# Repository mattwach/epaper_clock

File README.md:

# EPaper Clock and Weather Station

This project is an EPaper clock and weather station that automatically sets
itself (via GPS) and can be built to last about 6 months on 4 AAA batteries.
It purposefully does not need any network connections for the sake of security
and reliability.

Here is a video overview:

Features include:

   * Autoset (via GPS)
   * Current temperature.
   * Current humidity.
   * A pressure graph showing pressure over the last 25 hours.
   * Sunrise and Sunset times
   * Current moon phase
   * Select between 12h or 24h modes.
   * Select between English and metric units.

I put together two main variants of the project: "easy" and "low power".

The "easy" version is based on the Arduino Nano.  The intent with this
variation is to minimize cost and part count. The downside is that you'll need
to power the clock from a USB 5V adapter.

The "low power" version replaces the nano with a bare Atmega328P chip,
configured with a 32k crystal.  Under this configuration, the chip uses < 1
uA except when it is woken up by the crystal once per second.  This means
that the clock can be powered for a long time on batteries, even when power
draw from other devices is accounted for (all devices included draw 30-70
uA during while sleeping, and they are sleeping most of the time).

Both versions are designed to be buildable on a breadboard for experimentation.
The final board is designed to be buildable by any of several techniques:
prototype boards, CNC milling, chemical etchings, or ordering a PCB from the
provided design files are all options.

# Parts List

## "Easy" version

   * _Arduino Nano (or clone) ($3)_.  I went with a
     [clone board on Amazon](https://www.amazon.com/ELEGOO-Arduino-ATmega328P-Without-Compatible/dp/B0713XK923) but
     with April 2022 prices, I'd consider ebay as well.
   * _Waveshare 2.9 in EPaper Module ($22)_.  Purchase direct from Waveshare or
     [from amazon](https://www.amazon.com/2-9inch-Display-Module-Two-Color-Interface/dp/B07VD1V1YB).
   * _Adafruit MS8607 Pressure / Humidity / Temperature Sensor ($15)_.
     [link](https://www.adafruit.com/product/4716) I chose this one because of
     it's low power draw.
   * _Any basic GPS module with 9600 Baud TX_ ($12).  I went with
     [this one](https://smile.amazon.com/gp/product/B07P8YMVNT)
   * _Circuit Board_: This might be a
     [prototype board](https://www.amazon.com/ELEGOO-Prototype-Soldering-Compatible-Arduino/dp/B072Z7Y19F) OR
     [a piece of copper clad for CNC](https://www.amazon.com/MCIGICM-Copper-Laminate-Circuit-Single/dp/B01MCVLDDZ) OR
     you might opt to order a [prefabricated PCB](https://oshpark.com/).
   * _A couple of push switches_: [link](https://www.adafruit.com/product/1119)
     These are used to change the UTC time offset and display preferences.
   * _Materials to build a case_: I provide `.3mf`, `.scad`, and `.dxf` files
     if you would like to use a 3D printer, laser cutter, or CNC machine (I
     used a 3D printer and CNC), but you can also do a personalized case if you want.
   * _USB charger and cable_: To power the unit

## "Low Power" version

From the "easy" version above, you will need:

   * Waveshare 2.9 in EPaper Module
   * Adafruit MS8607 PHT monitor
   * Circuit board
   * Push switches
   * Case materials

You will also need

   * _Atmega328P DIP version ($2)_.
     [link](https://www.digikey.com/en/products/detail/microchip-technology/ATMEGA328P-PU/1914589)
     You can alternately opt for an SMD package version but soldering on the
     32k crystal will be harder.
   * _32768 Hz Crystal (<$1)_. [link](https://www.amazon.com/gp/product/B07Z2V95MJ)
     This oscillator is the key to low power in the design.
   * _Adafruit GPS Module ($30)_ [link](https://www.adafruit.com/product/746)
     This module is a bit higher quality than the one in the "easy" version in
     that it can track more satellites (for faster lock), provides and enable
     pin (for low power) and a port for keeping its memory active (for fast
     relock).  If all those features don't justify the added cost for you, you
     can hack a cheaper module to do the job by adding your own enable FET.  I
     explain how in upcoming steps.
   * _LED + Resistor_  The bare Atmega328P has no way to tell you if it's
     working, locked up, etc.  The blinking light thus provides a 1ms / second
     "heartbeat" that consumes almost no power but provides useful feedback.
     If you don't feel like you need it, you can omit it.
   * A couple of 10 uF and a 100 nF capacitors to smooth the power, which
     ranges from 50 uA to around 5-6 mA when refreshing the screen.
     If you feel lucky, you can try omitting these.
   * A 3x2 pin header for programming the chip via ICSP.  If you only program
     the chip off-board, you will not need this.
   * _Optional: A 1x2 pin header for UART debugging_.  You will only need this
     if the board is acting erratically.

## Arduino Mini version

I said there were two version but this is a bonus one (V2.5?).  It exists
because we live in a "parts drought" where chips like the Atmega328P go out of
stock for long periods.

You can run this version with the "easy" firmware or, if you have
the soldering confidence, you can solder a 32k crystal on the board and go with the
32k version of the firmware (more details on the next section).

Here is the schematic.  This one is wired with a "cheap GPS" solution but you
can also go with the Adafruit GPS if you replace the GPS part of the schematic
with the Adafruit setup (as illustrated in the low power schematic).

## Cheap GPS

That Adafruit GPS unit is expensive compared to the competition.  If you don't
think the added features (described above) are "worth it" you can drop in any
GPS module that transmits NMEA strings at 9600 baud (which is most of them).
**But now there is a new problem to solve:** most of these units lack an
enable/disable pin and GPS units typically consume 30-60 mA of power.  You can
hack a disable switch in using a N-MOSFET (or similar).  Here is the basic
idea:

[try it out](http://www.falstad.com/circuit/circuitjs.html?ctz=CQAgjCAMB0l3BWcMBMcUHYMGZIA4UA2ATmIxAUgoqoQFMBaMMAKADMLiUQUAWKwvx5Ds3MNCQwELAEoUMhEIIphuyqlSGSoUCSwBOSoczVCUfHZRYAPJQnJpeIDJAeuQTiwHEACgGUWACMlfHAUPGcwRRQwJ0gWAHd5RWVBATjEo3Ss8FUoFgBzHJQEFJFIOPzDBC5hTWJooSoweFkPZT5NUTqdTSpsaGxe3WkAZ3bPIV4GnuaQNgBDABtRugMPGc6NxVENZHg4Qu2QXePsbEUNFiA)

This power circuit has trade-offs.  See Appendix B for details if you are
interested in learning more about them.

## Low Power Hardware Mods

If running the "easy" version, you don't need to read this section.  For the
low power version, these mods will improve battery life significantly.

For illustration we will assume power is coming from a set of AAA batteries
which can supply 1000 mAh.  Let's assume you are using the 32k Adafruit version
and are doing no mods.  Here is an example power breakdown:

   * "Sleeping/Off" CPU, GPS, MS8607, and EPaper: Measured at 30-70 uA (we'll
     say 50uA)
   * Screen Update: 5 mA for 2 seconds once per minute: 5 * 2 / 60 = 166 uA
   * GPS Update: 50 mA for 10 seconds once per day: 50 * 10 / 86400 = 6 uA
   * MS8607 LED: 100 uA
   * Adafruit GPS pullup resistor: 500 uA

Thus we have 822 uA of average current draw which amounts to ~50 days of power.

Remove the MS8607 LED and the GPS pullup and we reduce power usage to 222 uA
which is ~187 days of power, significantly more!

### Remove the LED from the MS8607

### Remove the "pullup" enable resistor from the Adafruit GPS module (if using)

This was added by Adafruit to make the EN pin ignorable by inexperienced users.
But it has a big downside: when you pull it to ground (to disable the GPS) -
about 500uA is lost to heat in that pullup resistor!  Since the enable pin is
actively driven in the 32k oscillator design, you can remove the resistor.

### Pro mini mods

Google search "[Arduino mini low power](http://www.google.com?q=arduino%20mini%20low%20power)".
The TLDR is that you'll want to remove the voltage regulator and LED to reduce
power usage.  We are using the MS8607's voltage regulator (3.3V, 35-55 uA power
lost at idle) to power the pro mini.

In the photo above, I also removed the crystal oscillator (lower right) to prep
the chip for a 32K crystal.  This is *only* for the 32k crystal version and
*only after* the fuses have been changed on the pro mini as explained later.

## Other notes

The "easy" design actually contains the same firmware features from the 32k
design you can take advantage of if you want:

   1. D5 is still driven as a status light so you can connect an LED/Resistor
      here if you want to.
   2. D6 is still driven as a GPS enable/disable so you can use it to turn the
      GPS on/off if you want to.

# Firmware Upload

This firmware is open source and is located at [link here].

I have included prebuilt firmware `.hex` files in the `firmware/` directory so
you likely do not need to build the code.

Still want to build it and possibly add your own modifications?  Here are some
tips:

## OPTIONAL: Building the .hex firmware files yourself

Note that this code does not use Arduino libraries because the resulting code
would be too big to fit on the Atmega328P (and it's my personal preference).
Instead it's written in C using the same AVR base libraries that Arduino also
uses as a base.  If you want to compile the code, you will need to install the
(free) `avr-gcc` tools, then go to the `firmware/` directory and type

    make

If the code builds, you'll want to open the `Makefile` and look at
these options:

    # This is the Low-power stand alone chip configuration.
    CLOCK_MODE ?= USE_32K_CRYSTAL
    UART_MODE ?= HARDWARE_UART
    F_CPU ?= 8000000
    
    # This is the easy-to-build firmware that is based on an Ardino Nano
    #CLOCK_MODE ?= USE_CPU_CRYSTAL
    #UART_MODE ?= SOFTWARE_UART
    #F_CPU ?= 16000000

If you are building the 32k crystal firmware, you are done.  If building the
nano version, you'll need to comment out the 32k lines and uncomment the nano
lines, then `make` the firmware again.

There is also a special debug mode that dumps log messages over the hardware
UART at 9,600 baud.  I think you can ignore it for now but keep it in mind as
something that might be useful for troubleshooting later:

    # Uncomment to activate debug via the UART TX (9600 baud)
    #DEBUG_CFLAG := -DDEBUG

Finally, you can decide how often the GPS should be activated by changing a
couple of variables.  By default, currently runs once per day but will run less
often if GPS takes a long time to lock in order to reduce battery drain.  Read
all about it in `src/gps.c`

## ICSP hardware

This section is for those uploading code to a stand-alone Atmega328P chip (or
burning Arduino Pro mini fuses).

You'll need what is called an ISP (or ICSP) programmer.  You can buy these for
around $10 [on amazon](https://www.amazon.com/gp/product/B0885RKVMC) or make
one yourself with a spare
[Aruino Uno/Nano](https://create.arduino.cc/projecthub/arjun/programming-attiny85-with-arduino-uno-afb829)
The options continue but I'll leave that to a Google search for
"[Arduino ISP Programmer](http://www.google.com?q=Arduino%20ISP%20Programmer)".
I will note that a lot of these guides assume your real goal is to install a
bootloader but for our case, no bootloader is needed as you'll be uploading
the `.hex` file directly.

### Brownout detection

On my particular Atmega328P, the brownout detection as set to 3.5V (old version
of the chip?  A clone?) so I disabled
brownout detection with this command:

    /usr/bin/avrdude -patmega328p -cusbasp -Uefuse:w:0xFF:m

Your options may be different depending on your ISP programmer (the -c option).
You probably won't need it but just in case...

## Using avrdude

The popular Arduino IDE uses a free utility named `avrdude` to upload the hex files it creates to your
Uno/Nano/etc.  You can also download and use `avrdude` directly from the commandline
instead.  To get the correct options for the tool you can:

   1. Run an upload (blinking light demo or something) with the Arduino IDE
      with output logging turned on.  Then copy the command it used.  OR
   2. Read the official [avrdude docs](https://www.nongnu.org/avrdude/) OR
   3. Read one of the many many [avrdude tutorials](http://www.google.com?q=avrdude%20tutorial) on the internet.

For your reference, here is the `avrdude` command I used for the nano version (via `make upload`):

    /usr/bin/avrdude \
			-v \
			-patmega328p \
			-carduino \
			-P/dev/ttyUSB0 \
			-b57600 \
			-D \
			-Uflash:w:epaper_firmware_using_arduino_nano.hex:i 

and this is what I used for the ISP version:

    /usr/bin/avrdude \
			-v \
			-patmega328p \
			-cusbasp \
			-Uflash:w:epaper_firmware_using_arduino_nano.hex:i 

but there is a fair chance your setup is a bit different than mine.

## 32K Crystal

If you are building the "easy" version, skip this section.

If you are using the 32k crystal firmware, the crystal will need to be
installed for the firmware to operate.

**First (!)** You'll also want your ATMega328P set to use the internal 8 Mhz
crystal.  It's important to do this step first because the 32k crystal is using
the pins of the old crystal.  If you don't change these fuses, the chip will
become non responsive until you reconnect a 8 or 16 Mhz oscillator which
would be an annoying pain.  As far as I know the Arduino pro mini also needs
ISP to change the fuses (but I could be wrong).  I looked up "Arduino ISP" to
get the correct pin mappings for interfacing an ISP connector with a breadboard
as shown:

With my ISP programmer, I check with this command:

    $ avrdude -patmega328p -cusbasp
    ...
    avrdude: safemode: Fuses OK (E:FF, H:DE, L:E2)

The `L:E2` _is the setting you want for internal 8mhz_.  If your value is
different, you can update it with a command similar to this one:

    /usr/bin/avrdude -patmega328p -cusbasp -Ulfuse:w:0xE2:m

Then recheck.

Onto the hardware mod.  Here is a 32k crystal installed on a Atmega328P 

And on a Arduino Pro Mini (which also has the low power mods as-explained
earlier)

Attaching directly to the pins is recommended to reduce stray capacitance.  Too
much capacitance and the crystal will take longer to start oscillating (or fail
to start).

## Optional: First Steps

   * You can verify that things are OK so far on a breadboard by connecting
     just a LED/Resistor to D5 and uploading the firmware.  If all is well, the
     light will briefly flash once per second.
   * Next, you can add the EPaper display.  None of the data will be correct on
     the display but is should show something.
   * Next, add the PHT module
   * and finally the GPS module.

At this point, we are "done and can transfer everything over to a more permanent
fixture"

# Circuit Board assembly

Here you have the option of using a perf board, cutting the board with a CNC or
sending the design to a fab for manufacture.

The design files can be found in the `schematics/` directory and loaded into
Kicad.  There are three hardware flavors to choose from (all shown from behind
since that is how you would wire them by hand):

"Easy" Arduino Nano + Cheap GPS (always on)

Raw ATMega328P + Adafruit GPS (low power)

Pro Mini + Cheap GPS with MOSFET power cutoff

As can bee seen above, I cut the ATMega328P version with my CNC machine.  If
you have not used CNC to cut a PCB and are interested, try a google search for
"[3018 PCB](http://www.google.com?q=3018%20PCB)" and you'll
find many videos and articles on the topic.  I may do my own tutorial in a
separate article in the future but, since CNC is optional here it's not a good
place to go into details.  Isolation clearances are 0.4mm but you can go
narrower (probably not wider).  I used Flatcam to convert Kicad's Gerber output
to G-Code.  I included my Flatcam project in the schematic directory.  I also
included the G-Code files I sent to my 3018 CNC machine.  If you have a 3018
CNC, you can probably directly use the G-Code files, but do a "dry" run without
a bit first to make sure things look sane.

Anyway, when the circuit is finished and put together, it should function like
it did on the breadboard.  If you hold the select button on startup,
the GPS will be powered down (if possible) and you can try measuring the
current draw with your multimeter.  If you see 50-110 uA, we are seeing the
same result.  If not, you can unplug devices one at a time to try and narrow
down the parasitic power draw (assuming you didn't solder everything
permanently to the board).

# Case Design

You can design any type of case you want and I encourage you to be creative
here!  But I'll also share how I made my case and provide all of the files in
case you are interested in a more streamlined progression.

All of my design files are in the `case_design/` folder of the project.

My design uses a 3D printed support structure and two CNC parts: a top cover
and front panel.  The CNC parts are made of wood because I thought it would
look nicer than plastic.  I designed the whole thing upfront in OpenSCAD

I printed the main structure with 0.2mm layer height.  On my printer, the print
took a little over 5 hours.

I used OpenSCAD's "projection" feature to created 2D DXF files for the top
cover and front plate.  At this point, I would normally use a free program
called "Carbide Create" to make G-Code for the CNC machine.  But my face plate
has a 45 degree chamfer to the screen and Carbide Create is too basic of a
program to handle this well (at least my Google searches through forums on
    their website led me to that conclusion).  So I tried a different program
called "CamBam" and it worked very well.  CamBam is not free but you can use it
40 times for free.  I'm leaning toward purchasing the program but want to
experiment with it on a few more project first.

Some build photos:

# Appendix A: Optional Clock Drift Correction

Your 32k/CPU crystal will not be perfect.  When the GPS turns on, it will
correct the drift.  But if the drift is bad or your GPS signal is bad, you can
also apply a correction in the firmware.  This currently requires you to build
the code.

At the top of `main.c` there are some commented out defines:

    // Clock drift correction
    // If your clock runs too fast or too slow, then you can enable these
    //#define CORRECT_CLOCK_DRIFT
    // number of seconds that a second should be added or removed
    //#define CLOCK_DRIFT_SECONDS_PER_CORRECT 1800
    // define this if the clock is too slow, otherwise leave it commented out
    //#define CLOCK_DRIFT_TOO_SLOW

You can uncomment all of the `#define` statements above to enable the correction.
You only uncomment `CLOCK_DRIFT_TOO_SLOW` of your clock is falling behind.
If your clock is too fast, leave it commented.

The only thing left to do is set `CLOCK_DRIFT_SECONDS_PER_CORRECT`...

### The math way

Wait a handful of hours, then see how much the clock has drifted.  For example,
you might wait 23 hours.  If at that point you see the clock has lost 10
seconds, then your correction would be: (3600 * 23) / 10 = 8280 seconds
per correction.

    #define CORRECT_CLOCK_DRIFT
    #define CLOCK_DRIFT_SECONDS_PER_CORRECT 8280
    #define CLOCK_DRIFT_TOO_SLOW

If you already set `CLOCK_DRIFT_SECONDS_PER_CORRECT` and find you want to fine
tune it _even more_, then you need to add (if too slow) or subtract (if too
fast) `int(SECONDS_ON / CLOCK_DRIFT_SECONDS_PER_CORRECT)` to the error term
in the denominator to account for the already-corrected error seconds.
Building on the example above, if _we were still_ 2 seconds slow after 20
hours, the calculation would be.  (3600 * 20) / (int(3600 * 20 / 8280) + 2) =
7200.

### The non math way

Just try a number like 5,000 and refine it as you note that the clock is still
to fast or too slow.  Still too slow?  Try 2,500.  Too fast?  Try 10,000.  Keep
notes and iteratively refine it to some acceptable value just like the number
guessing games you may have played at some point.

# Appendix B: Cheap GPS power control (The tale of the BS170 N-MOSFET)

Revisiting the power control circuit described in the "Cheap GPS" section.

[try it out](http://www.falstad.com/circuit/circuitjs.html?ctz=CQAgjCAMB0l3BWcMBMcUHYMGZIA4UA2ATmIxAUgoqoQFMBaMMAKADMLiUQUAWKwvx5Ds3MNCQwELAEoUMhEIIphuyqlSGSoUCSwBOSoczVCUfHZRYAPJQnJpeIDJAeuQTiwHEACgGUWACMlfHAUPGcwRRQwJ0gWAHd5RWVBATjEo3Ss8FUoFgBzHJQEFJFIOPzDBC5hTWJooSoweFkPZT5NUTqdTSpsaGxe3WkAZ3bPIV4GnuaQNgBDABtRugMPGc6NxVENZHg4Qu2QXePsbEUNFiA)

The power cutoff circuit above is called a "low side switch".  It's benefit is
that it's relatively easy to understand and the part count is low.  That said,
there are some design concerns:

   * The ground of the GPS is not tied to GND but on the MOSFET drain.  This 
     means that the UART signal from the GPS to the microcontroler will have
     the MOSFET voltage drop added to it (Vds), increasing noise sensitivity
     and possibly causing outright errors. 
   * You would not want to use this design if your microcontroller inputs
     are specified as 3.3V maximum (the ATMega328P I chose doesn't have this
     limitation).
   * 3.3V (EN pin above) is not a very strong turn-on voltage for a typical MOSFET.

But hey, the UART is a digital signal and the ground difference isn't *that*
much so maybe it will work anyway?  I tried it and it worked fine... at first
but I came to discover over time that it was not reliable.  To understand
*why*, we refer to the characteristic curves of the BS170 I originally chose as
my N-MOSFET:

At 3.3V on the X axis we will be sitting between the 3.0 and 4.0V lines on the
graph.  So maybe we'll get 100mA?  Maybe enough?

My multimeter was telling me the GPS consumes 40-60ma while on but I think this
is an average value.  Depending on what the GPS was trying to do, it just
needed more current than the transistor was willing to allow, thus the GPS
ground (MOSFET drain) voltage would rise.  This created both UART errors and
reduced overall voltage to the GPS unit which would sometimes still sort of
work and other times go into a reset loop.

One solution would be to go with a "high side" with an additional P-MOSFET on
top to make it happen.  This eliminates the separate ground issue and provides
a full 5V (battery) gate voltage swing, which will turn the associated P-MOSFET
fully on:

[try it out](http://www.falstad.com/circuit/circuitjs.html?ctz=CQAgjCAMB0l3BWcMBMcUHYMGZIA4UA2ATmIxAUgoqoQFMBaMMAKADMLiUQUAWKwvx5Ds3MNCQxIKdiEFUwGQnKFgUeELwjjJsGQCcVCpRULHlC+JBYB3OX3DrTCp9bsIzjjR-NQWAJWcvTWJlNQ0qKiFJKCgJFkMMNHATJKp1CJoWAA8QHHIiDQw8AowIXmEQAHEABQBlFgAjOTwNMC480J5ivwBzPOSMgapRSL87Qg9gtOC3YenkxQtbIxTleR4Ha36NlCmN3ArIhM5uPiiu89iweADNQWEo0UfYqJHobFe4hBYAZ3uKldeJchAoQGwAIYAG1+dBYQA)

But in my optimism, I had already ordered PCBs with the lowside wiring so my
secondary solution was to abandon the BS170 and go with a FQP30N06L instead.
This higher-current MOSFET (max 30A!) seems like serious overkill, and it is
but its curves look like this:

Around 10A of current allowance at 3.3V which is a 100x improvement over the
BS170 and should now be plenty.  And indeed the instabilities have not
returned.

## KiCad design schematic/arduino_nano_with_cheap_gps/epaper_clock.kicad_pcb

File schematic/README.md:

Different Hardware Configurations:

   * `arduino_nano_with_cheap_gps`:  The "easy" design which uses a minimum part count
     and is intended to be powered with a USB power adapter.
   * `raw_atmega328p_with_adafruit_gps`: Uses raw Atmega328P and an Adafruit
       GPS unit.  A good match for the 32k oscillator firmware for long battery life.
   * `arduino_pro_mini_with_cheap_gps`: Uses an arduino pro mini with an inexpensive GPS
      unit and MOSFET shutoff.  The pro mini can be hacked with with a 32k oscillator
      (see the main README.md for more info)  

You can mix and match above, for example raw atmega328p + cheap gps, but will need to make
layout corrections (or make a simple adapter board) if you are using the PCB layout.

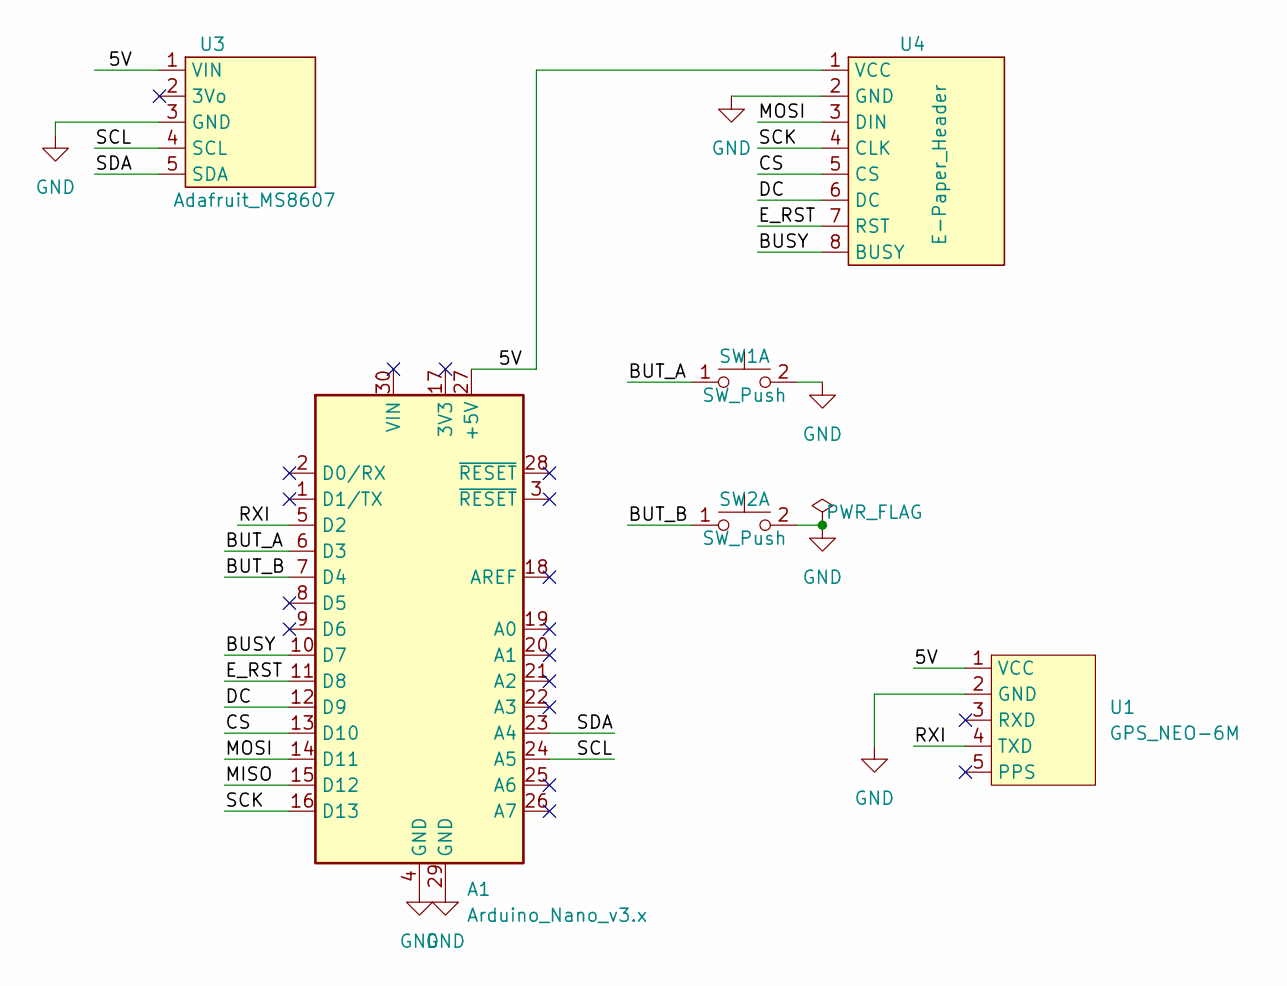
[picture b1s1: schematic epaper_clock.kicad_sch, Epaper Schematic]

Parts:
A1: Arduino_Nano_v3.x; Arduino_Nano
SW1, SW2: SW_Push; SW_TH_Tactile_Omron_B3F-10xx
U1: GPS_NEO-6M
U3: Adafruit_MS8607
U4: E-Paper_Header; PinHeader_1x08_P2.54mm_Vertical

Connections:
/5V: A1.27 (+5V), U1.1 (VCC), U3.1 (VIN), U4.1 (VCC)
/BUSY: A1.10 (D7), U4.8 (BUSY)
/BUT_A: A1.6 (D3), SW1.1 (C)
/BUT_B: A1.7 (D4), SW2.1 (C)
/CS: A1.13 (D10), U4.5 (CS)
/DC: A1.12 (D9), U4.6 (DC)
/E_RST: A1.11 (D8), U4.7 (RST)
/MISO: A1.15 (D12)
/MOSI: A1.14 (D11), U4.3 (DIN)
/RXI: A1.5 (D2), U1.4 (TXD)
/SCK: A1.16 (D13), U4.4 (CLK)
/SCL: A1.24 (A5), U3.4 (SCL)
/SDA: A1.23 (A4), U3.5 (SDA)
GND: A1.4 (GND), A1.29 (GND), SW1.2 (D), SW2.2 (D), U1.2 (GND), U3.3 (GND), U4.2 (GND)

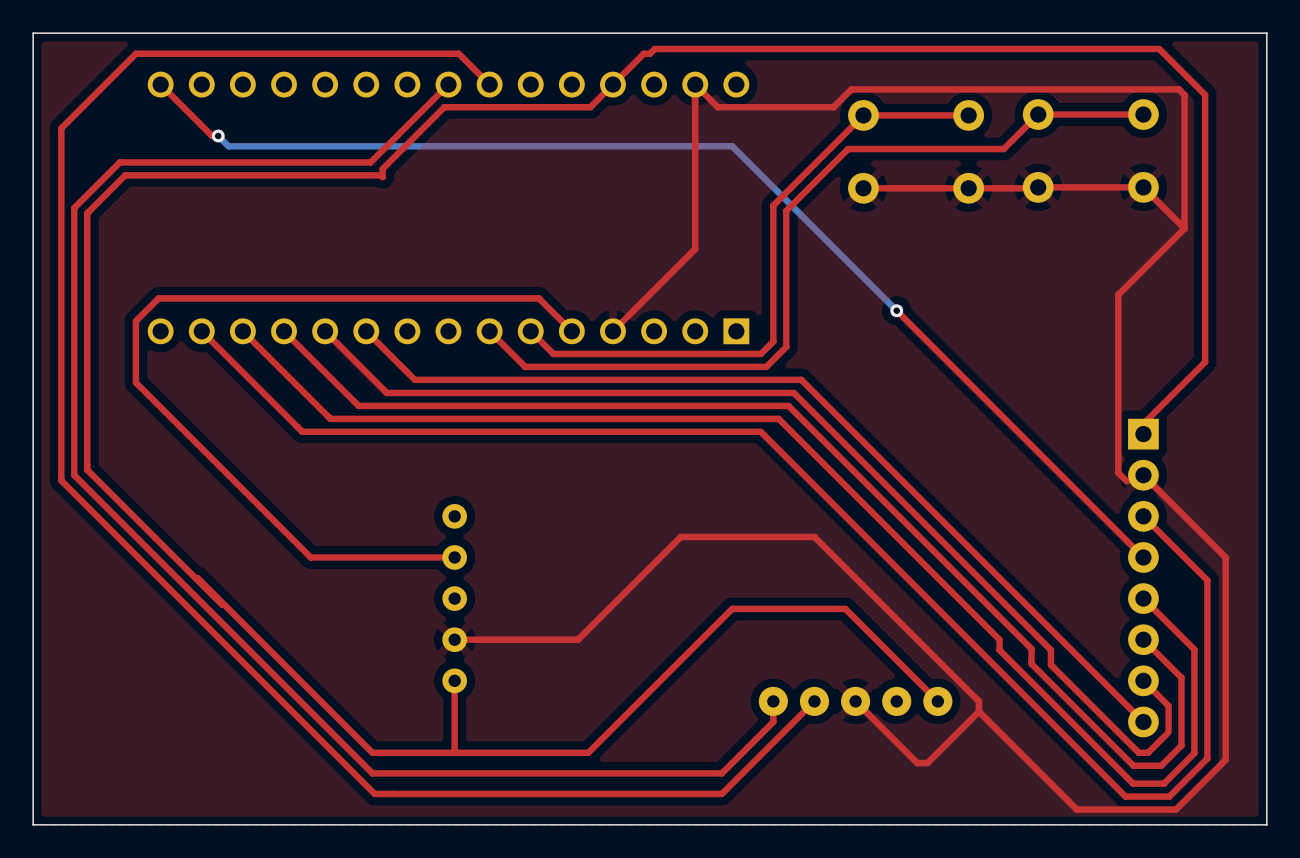
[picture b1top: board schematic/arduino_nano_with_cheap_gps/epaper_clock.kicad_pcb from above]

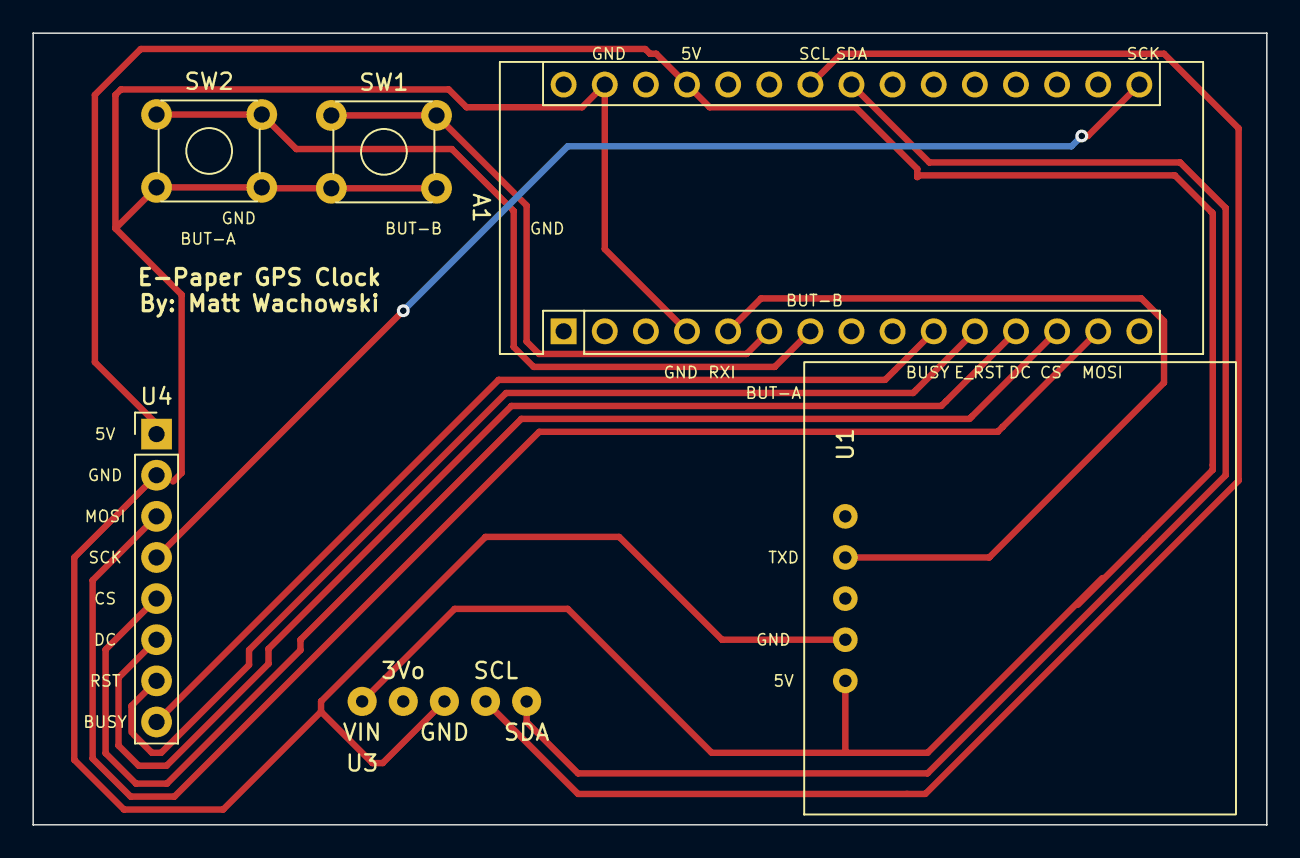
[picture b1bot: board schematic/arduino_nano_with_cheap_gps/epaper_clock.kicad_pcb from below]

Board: 2 copper layers, 76.2 x 48.9 mm, 6 parts (6 on the bottom side), 13 nets.

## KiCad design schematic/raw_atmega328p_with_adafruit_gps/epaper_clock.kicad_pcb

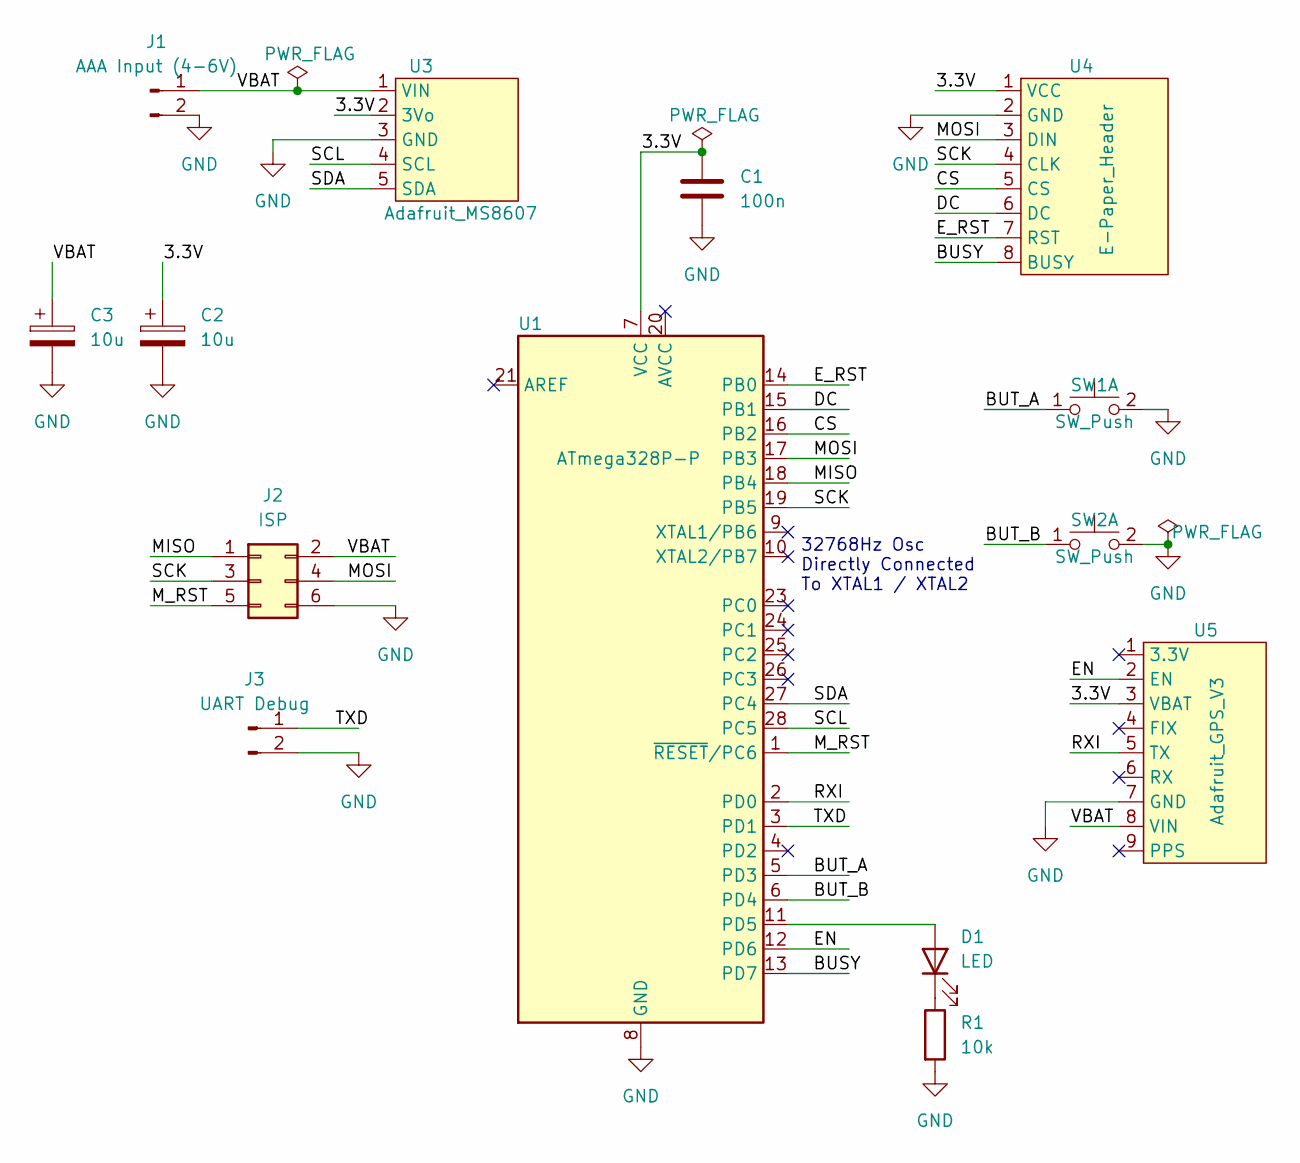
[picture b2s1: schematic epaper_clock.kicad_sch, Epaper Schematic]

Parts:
C1: 100n; C_Disc_D5.0mm_W2.5mm_P2.50mm
C2, C3: 10u; CP_Radial_D6.3mm_P2.50mm
D1: LED; LED_D3.0mm
J1: AAA Input (4-6V); PinHeader_1x02_P2.54mm_Vertical
J2: ISP; PinHeader_2x03_P2.54mm_Vertical
J3: UART Debug; PinHeader_1x02_P2.54mm_Vertical
R1: 10k; R_Axial_DIN0411_L9.9mm_D3.6mm_P7.62mm_Vertical
SW1, SW2: SW_Push; SW_TH_Tactile_Omron_B3F-10xx
U1: ATmega328P-P; DIP-28_W7.62mm
U3: Adafruit_MS8607
U4: E-Paper_Header; PinHeader_1x08_P2.54mm_Vertical
U5: Adafruit_GPS_V3

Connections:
/3.3V: C1.1, C2.1, U1.7 (VCC), U3.2 (3Vo), U4.1 (VCC), U5.3 (VBAT)
/BUSY: U1.13 (PD7), U4.8 (BUSY)
/BUT_A: SW1.1 (C), U1.5 (PD3)
/BUT_B: SW2.1 (C), U1.6 (PD4)
/CS: U1.16 (PB2), U4.5 (CS)
/DC: U1.15 (PB1), U4.6 (DC)
/EN: U1.12 (PD6), U5.2 (EN)
/E_RST: U1.14 (PB0), U4.7 (RST)
/MISO: J2.1, U1.18 (PB4)
/MOSI: J2.4, U1.17 (PB3), U4.3 (DIN)
/M_RST: J2.5, U1.1 (~RESET/PC6)
/RXI: U1.2 (PD0), U5.5 (TX)
/SCK: J2.3, U1.19 (PB5), U4.4 (CLK)
/SCL: U1.28 (PC5), U3.4 (SCL)
/SDA: U1.27 (PC4), U3.5 (SDA)
/TXD: J3.1, U1.3 (PD1)
/VBAT: C3.1, J1.1, J2.2, U3.1 (VIN), U5.8 (VIN)
GND: C1.2, C2.2, C3.2, J1.2, J2.6, J3.2, R1.2, SW1.2 (D), SW2.2 (D), U1.8 (GND), U1.22 (GND), U3.3 (GND), U4.2 (GND), U5.7 (GND)
unnamed: D1.1 (K), R1.1
unnamed: D1.2 (A), U1.11 (PD5)

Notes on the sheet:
32768Hz Osc Directly Connected To XTAL1 / XTAL2

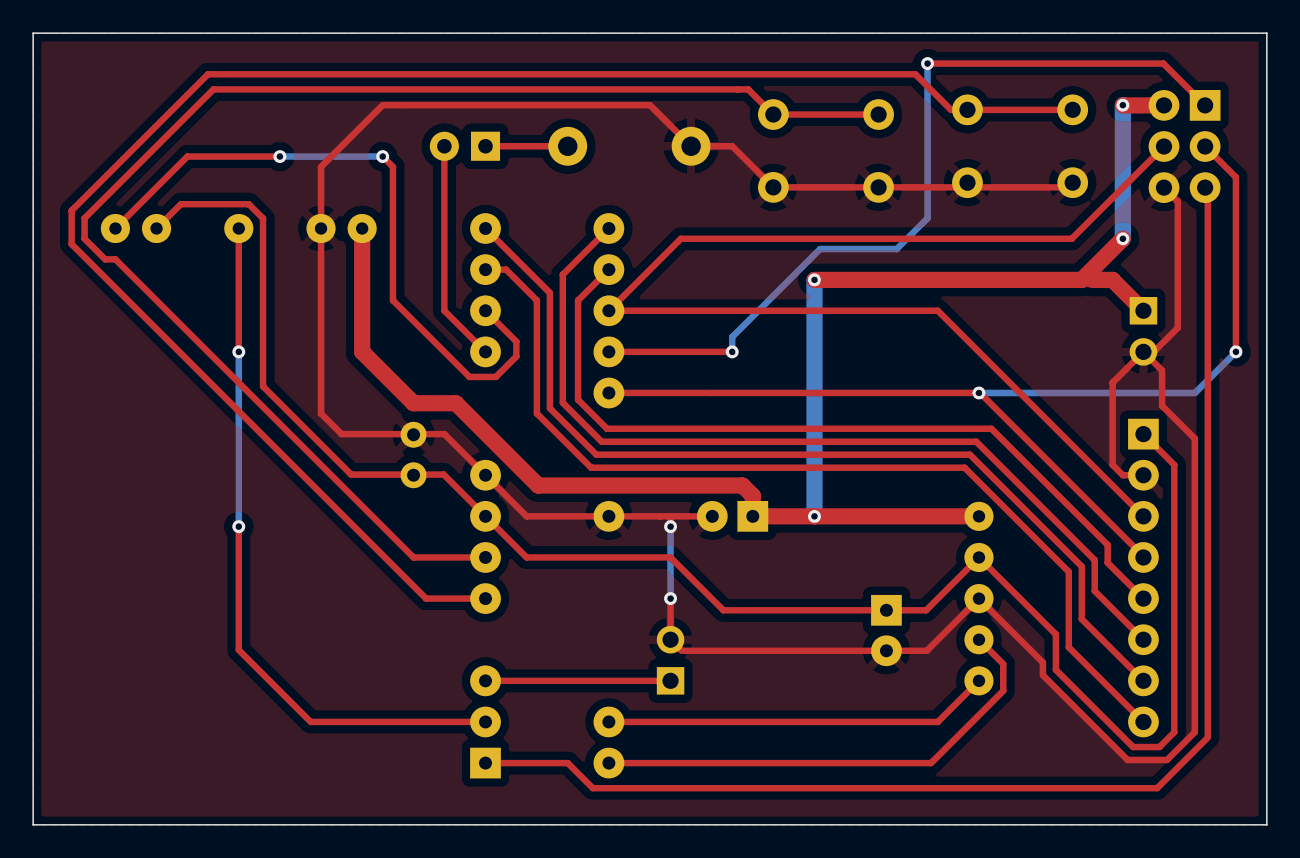
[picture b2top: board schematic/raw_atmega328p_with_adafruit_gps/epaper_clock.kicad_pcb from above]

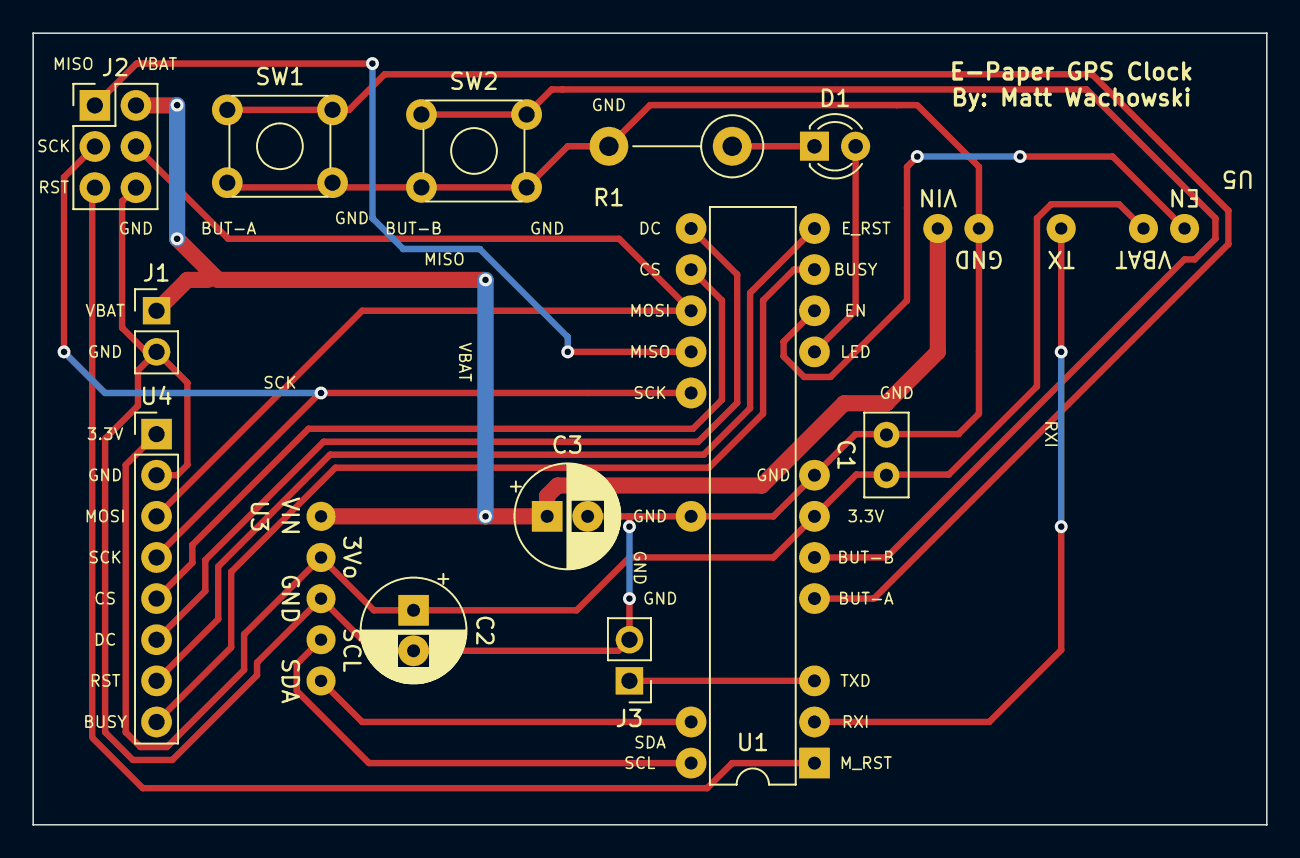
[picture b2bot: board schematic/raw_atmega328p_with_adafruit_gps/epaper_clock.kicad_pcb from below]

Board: 2 copper layers, 76.2 x 48.9 mm, 14 parts (14 on the bottom side), 20 nets.

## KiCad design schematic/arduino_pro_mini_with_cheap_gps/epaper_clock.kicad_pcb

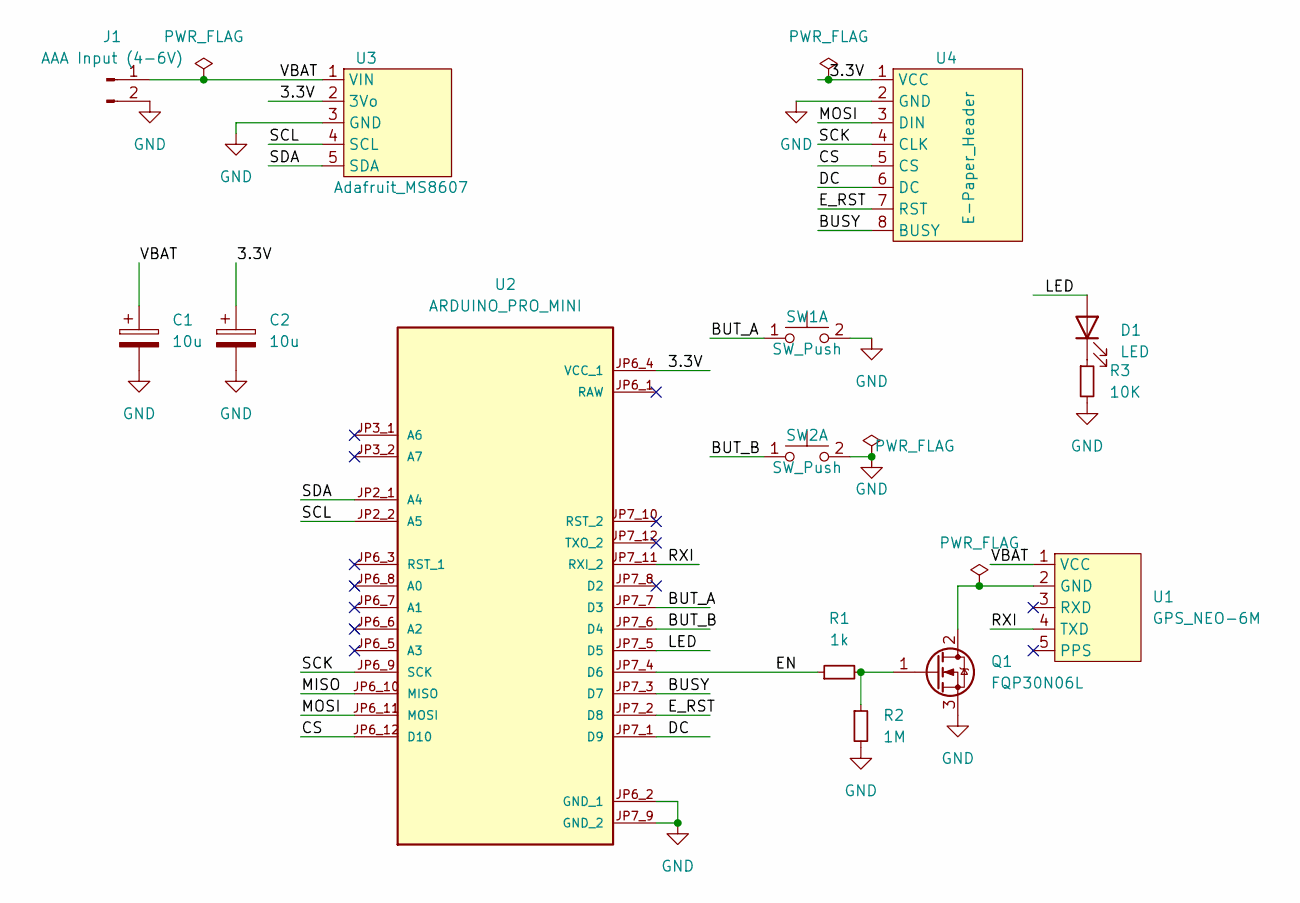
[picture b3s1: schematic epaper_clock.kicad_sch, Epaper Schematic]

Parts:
C1, C2: 10u; CP_Radial_D6.3mm_P2.50mm
D1: LED; LED_D3.0mm
J1: AAA Input (4-6V); PinHeader_1x02_P2.54mm_Vertical
Q1: FQP30N06L; TO-220-3_Vertical
R1: 1k; R_Axial_DIN0204_L3.6mm_D1.6mm_P5.08mm_Horizontal
R2: 1M; R_Axial_DIN0204_L3.6mm_D1.6mm_P5.08mm_Horizontal
R3: 10K; R_Axial_DIN0204_L3.6mm_D1.6mm_P5.08mm_Horizontal
SW1, SW2: SW_Push; SW_TH_Tactile_Omron_B3F-10xx
U1: GPS_NEO-6M
U2: ARDUINO_PRO_MINI; MODULE_ARDUINO_PRO_MINI; PARTREV N/A
U3: Adafruit_MS8607
U4: E-Paper_Header; PinHeader_1x08_P2.54mm_Vertical

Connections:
/3.3V: C2.1, U2.JP6_4 (VCC_1), U3.2 (3Vo), U4.1 (VCC)
/BUSY: U2.JP7_3 (D7), U4.8 (BUSY)
/BUT_A: SW1.1 (C), U2.JP7_7 (D3)
/BUT_B: SW2.1 (C), U2.JP7_6 (D4)
/CS: U2.JP6_12 (D10), U4.5 (CS)
/DC: U2.JP7_1 (D9), U4.6 (DC)
/EN: R1.1, U2.JP7_4 (D6)
/E_RST: U2.JP7_2 (D8), U4.7 (RST)
/LED: D1.2 (A), U2.JP7_5 (D5)
/MISO: U2.JP6_10 (MISO)
/MOSI: U2.JP6_11 (MOSI), U4.3 (DIN)
/RXI: U1.4 (TXD), U2.JP7_11 (RXI_2)
/SCK: U2.JP6_9 (SCK), U4.4 (CLK)
/SCL: U2.JP2_2 (A5), U3.4 (SCL)
/SDA: U2.JP2_1 (A4), U3.5 (SDA)
/VBAT: C1.1, J1.1, U1.1 (VCC), U3.1 (VIN)
GND: C1.2, C2.2, J1.2, Q1.3 (S), R2.2, R3.2, SW1.2 (D), SW2.2 (D), U2.JP6_2 (GND_1), U2.JP7_9 (GND_2), U3.3 (GND), U4.2 (GND)
unnamed: D1.1 (K), R3.1
unnamed: Q1.1 (G), R1.2, R2.1
unnamed: Q1.2 (D), U1.2 (GND)

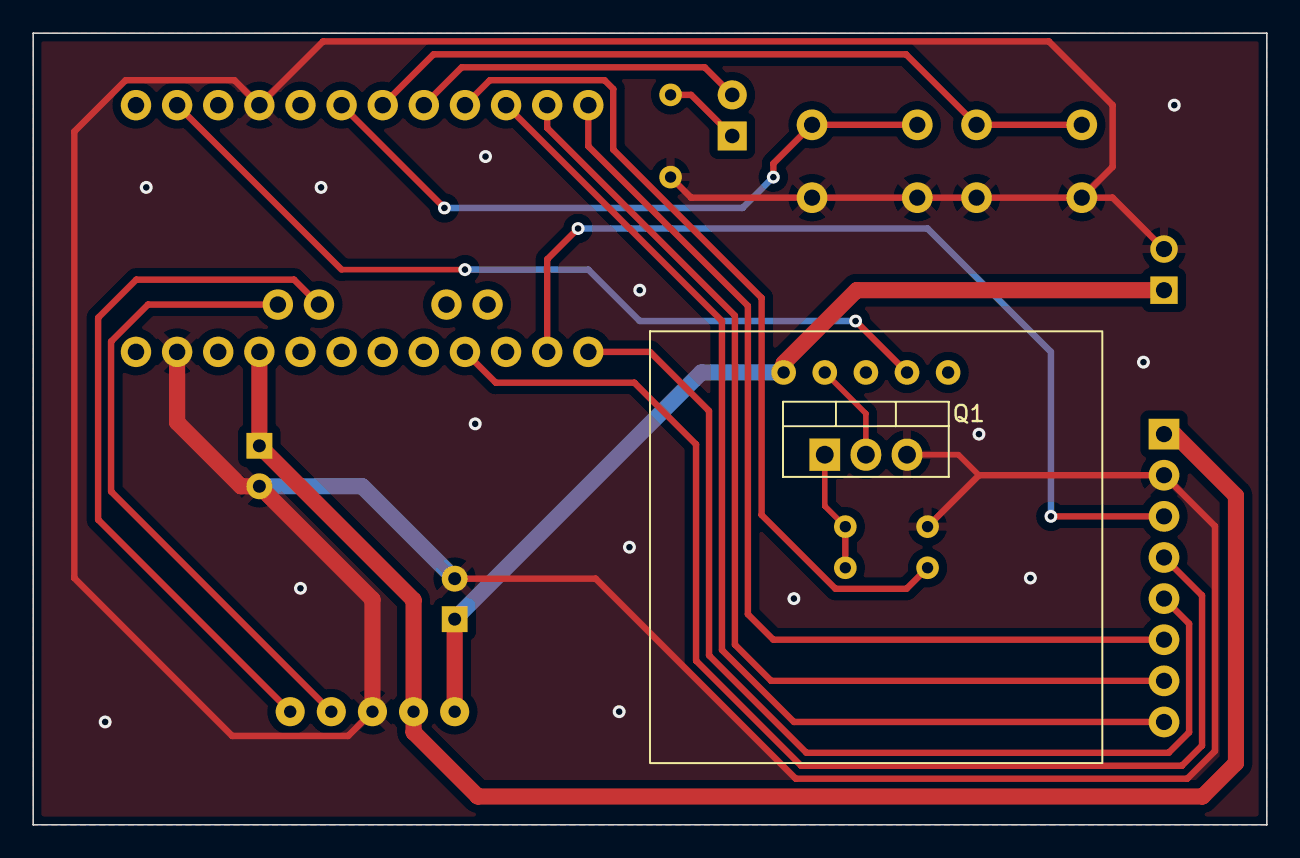
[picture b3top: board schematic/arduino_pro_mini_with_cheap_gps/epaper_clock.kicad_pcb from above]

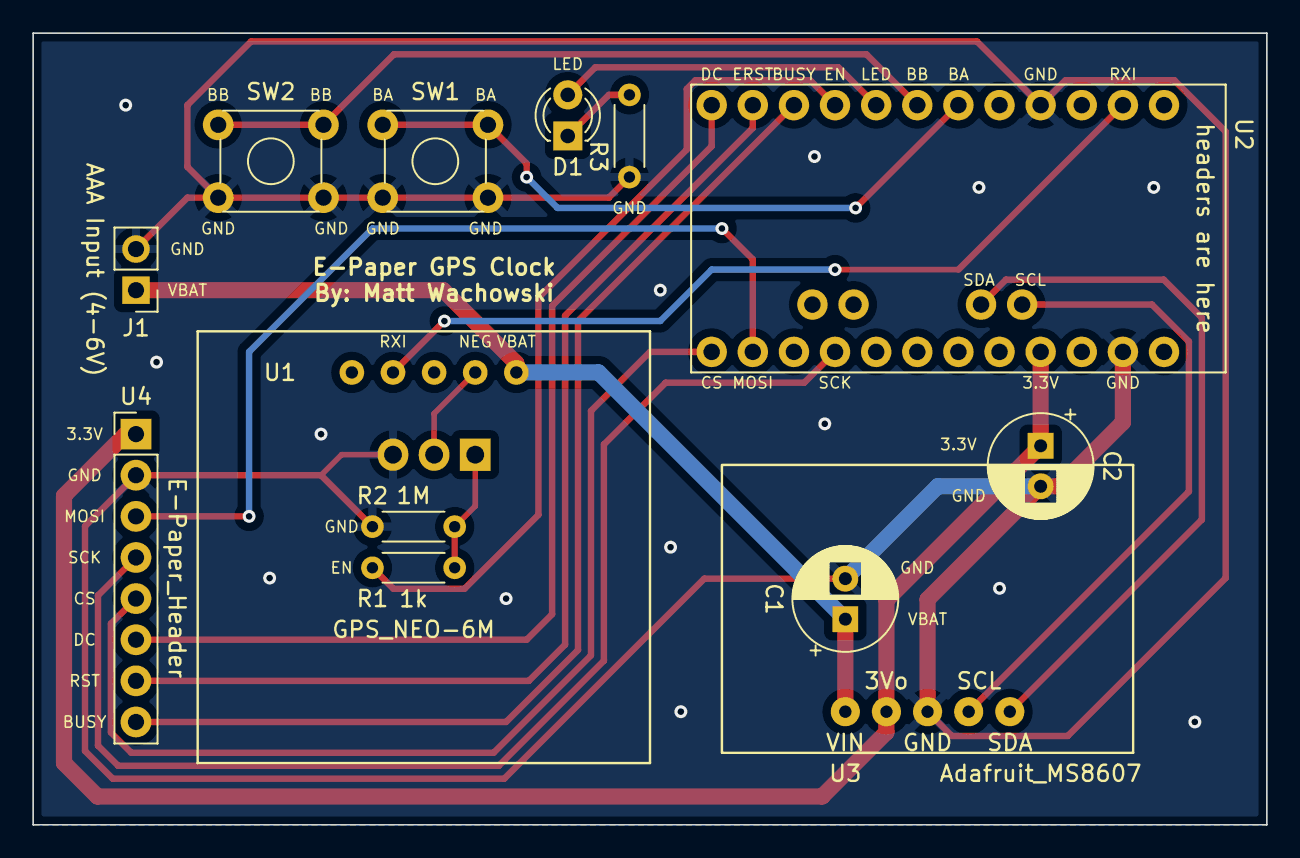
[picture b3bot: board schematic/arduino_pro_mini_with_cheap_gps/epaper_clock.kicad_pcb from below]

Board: 2 copper layers, 76.2 x 48.9 mm, 14 parts (12 on the bottom side), 19 nets.

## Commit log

2022-04-21 Initial snapshot from my private repo.
2022-04-22 Added video overview link
2022-05-14 Removed computer-specific paths.
2022-05-14 Clean up avr paths to make them easier to run on non-linux platforms.
2022-05-18 Fixed UTC offset range.
    It was 0 to 23 but should have been -12 to 14.
2022-05-18 Added missing avrdude.conf
    This is also included with avrdude but the "make upload" step assumes
    there is a local copy.
2022-05-25 Correct moon phase assignment.
2022-05-25 Update firmware files with moon phase fix.
2022-07-09 Adding a new build for an arduino pro mini 3.3V @ 8mhz.
2022-07-10 Fix arduino pro mini hex file (accidently copied the elf file).
2022-12-02 Added workaround for GCC12 error
